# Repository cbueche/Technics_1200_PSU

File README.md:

# DC PSU for the Technics SL-1200 

An external PSU (linear power supply unit) for the Technics SL-1200 turntable. Originaly designed by user 6L6 published on DIYaudio.com forum in 2013.

## License

This project is licensed under the terms of the CERN Open Hardware Licence Version 2, permissive variant [CERN-OHL-P](cern_ohl_p_v2).

## Schematics

The [schematic](schema_v4.pdf) is an export from the kicad files.

## PCB

I designed a PCB for this project, the [kicad](kicad/) directory contains everything needed : the schematic, the PCB design, etc. I updated those files to Kicad 8. There is a zip file that I was able to use to order 5 PCBs from PCBway, the minimal order quantity was 5 in May 2023. The four remaining PCBs were sold quickly.

The side-holes are not connected to anything, proper grounding is your task. I recommend connecting the input earth to the case. As designed, the DC output (GND and Vcc) are floating.

## BOM

Sorry, no BOM, see the CSV file in the [kicad](kicad/) directory, the footprint column provides some info on the spacing. In general, very standard components can be used. Big capacitors are 10mm snap-in, connectors use 7.5mm spacing.

## Resources

- the [original thread](https://www.diyaudio.com/community/threads/technics-sl-1200-dc-power-supply.238618/) on DIYaudio
- original author : 6L6, DIYaudio.com

## concept used in my personal case

- external DC PSU unit
- regulator and probe switch from [KAB USA](https://www.kabusa.com)

## case

The original transformer and this PCB did somewhat tightly fit into a Hifi 2000 Galaxy case model GX183 (80x124x230). A tight fit so check before drilling holes.

## fuses

These fuse values are appropriate for 230V.

- top, input : AC, T 250 mA
- bottom, output : DC, T 1 A

## DC cable

- 2 x 0.75
- pin 1 : brown : GND
- pin 2 : blue : Vcc

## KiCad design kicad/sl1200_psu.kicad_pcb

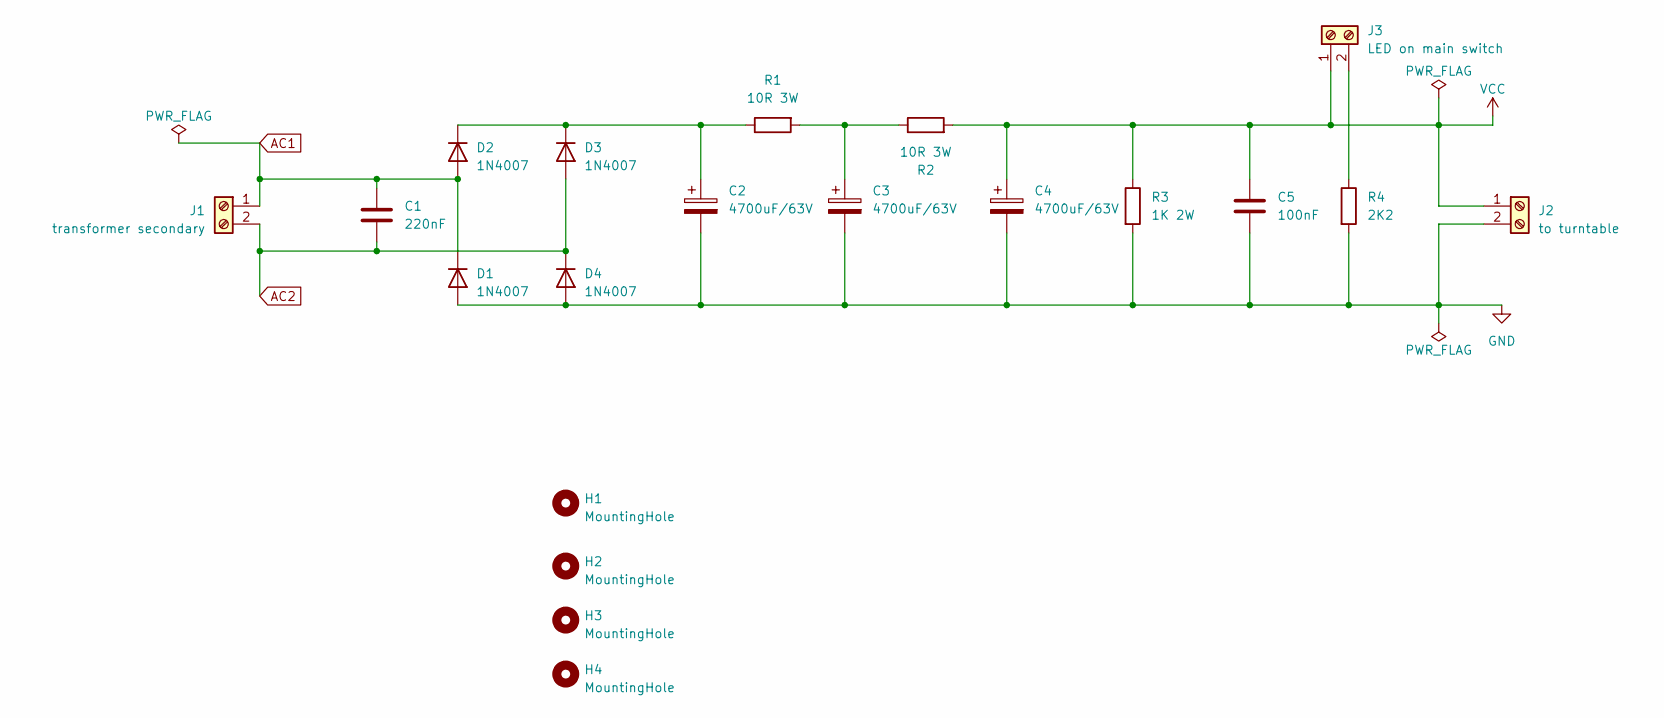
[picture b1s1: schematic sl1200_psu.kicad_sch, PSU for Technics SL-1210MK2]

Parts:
C1: 220nF; C_Rect_L26.5mm_W6.0mm_P22.50mm_MKS4
C2, C3, C4: 4700uF/63V; CP_Radial_D26.0mm_P10.00mm_SnapIn
C5: 100nF; C_Rect_L18.0mm_W6.0mm_P15.00mm_FKS3_FKP3
D1, D2, D3, D4: 1N4007; D_DO-41_SOD81_P10.16mm_Horizontal
H1, H2, H3, H4: MountingHole; MountingHole_3.2mm_M3
J1: transformer secondary; TerminalBlock_RND_205-00067_1x02_P7.50mm_Horizontal
J2: to turntable; TerminalBlock_RND_205-00067_1x02_P7.50mm_Horizontal
J3: LED on main switch; TerminalBlock_RND_205-00067_1x02_P7.50mm_Horizontal
R1, R2: 10R 3W; R_Axial_Power_L25.0mm_W9.0mm_P7.62mm_Vertical
R3: 1K 2W; R_Axial_Power_L20.0mm_W6.4mm_P5.08mm_Vertical
R4: 2K2; R_Axial_DIN0414_L11.9mm_D4.5mm_P5.08mm_Vertical

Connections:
AC1: C1.1, D1.1 (K), D2.2 (A), J1.1
AC2: C1.2, D3.2 (A), D4.1 (K), J1.2
GND: C2.2, C3.2, C4.2, C5.2, D1.2 (A), D4.2 (A), J2.2, R3.2, R4.2
unnamed: C3.1, R1.2, R2.1
unnamed: C2.1, D2.1 (K), D3.1 (K), R1.1
unnamed: J3.2, R4.1
VCC: C4.1, C5.1, J2.1, J3.1, R2.2, R3.1

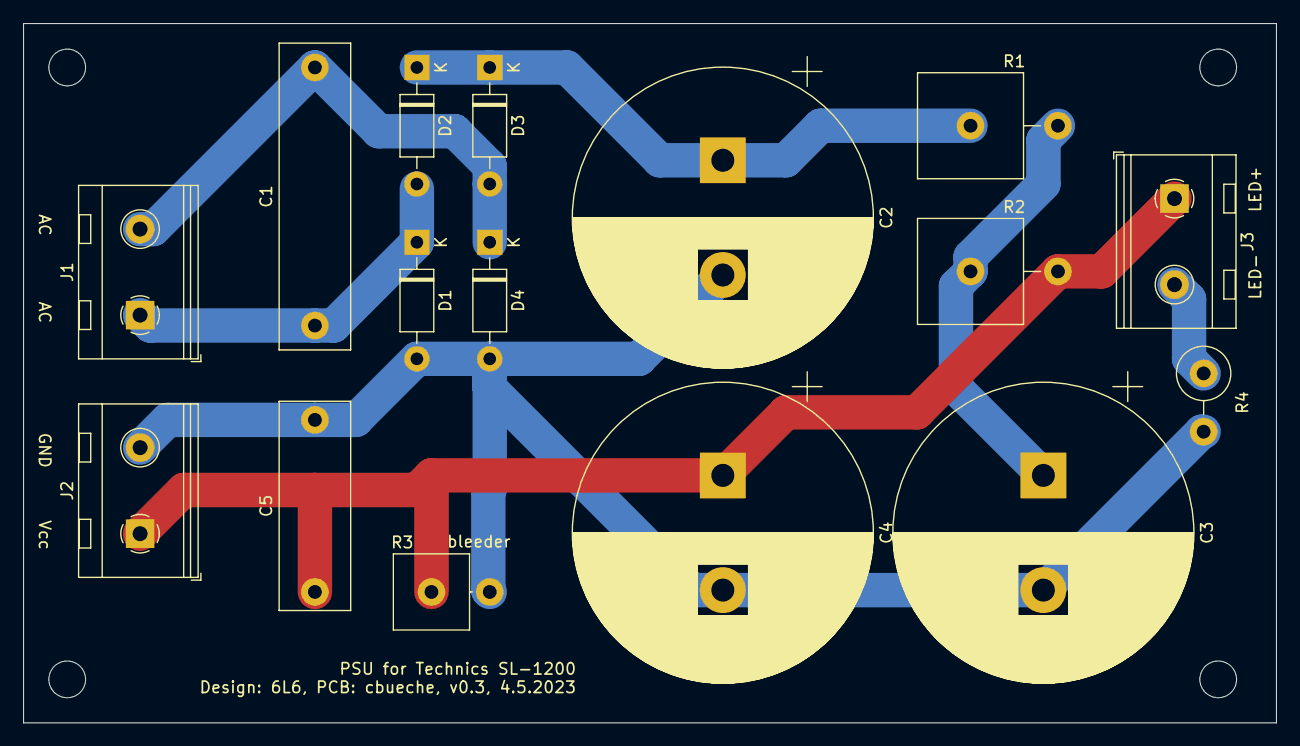
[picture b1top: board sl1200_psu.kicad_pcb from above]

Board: 2 copper layers, 109.2 x 61.0 mm, 20 parts (0 on the bottom side), 7 nets.

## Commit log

2024-04-18 typo
